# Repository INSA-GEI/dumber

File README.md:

# Dumber

Depot du projet de temps reel 4eme année au departement GEI de l'INSA Toulouse.

## Repertoires
- hardware : contient les plans pour la partie mecanique du robot et de son chargeur, ainsi que les plans de conception des PCB du robot, du chargeur, de l'adaptateur Xbee pour la raspberry  et les plans des CAP du robot
- software: rassemble les parties logicielles du robot, du chargeur, les bibliotheques et superviseur coté raspberry et l'interface Web
- doc: contient les sujets de TD et TP
- aruco_markers: Script de generation des tags (aruco) utilisés sur les robots

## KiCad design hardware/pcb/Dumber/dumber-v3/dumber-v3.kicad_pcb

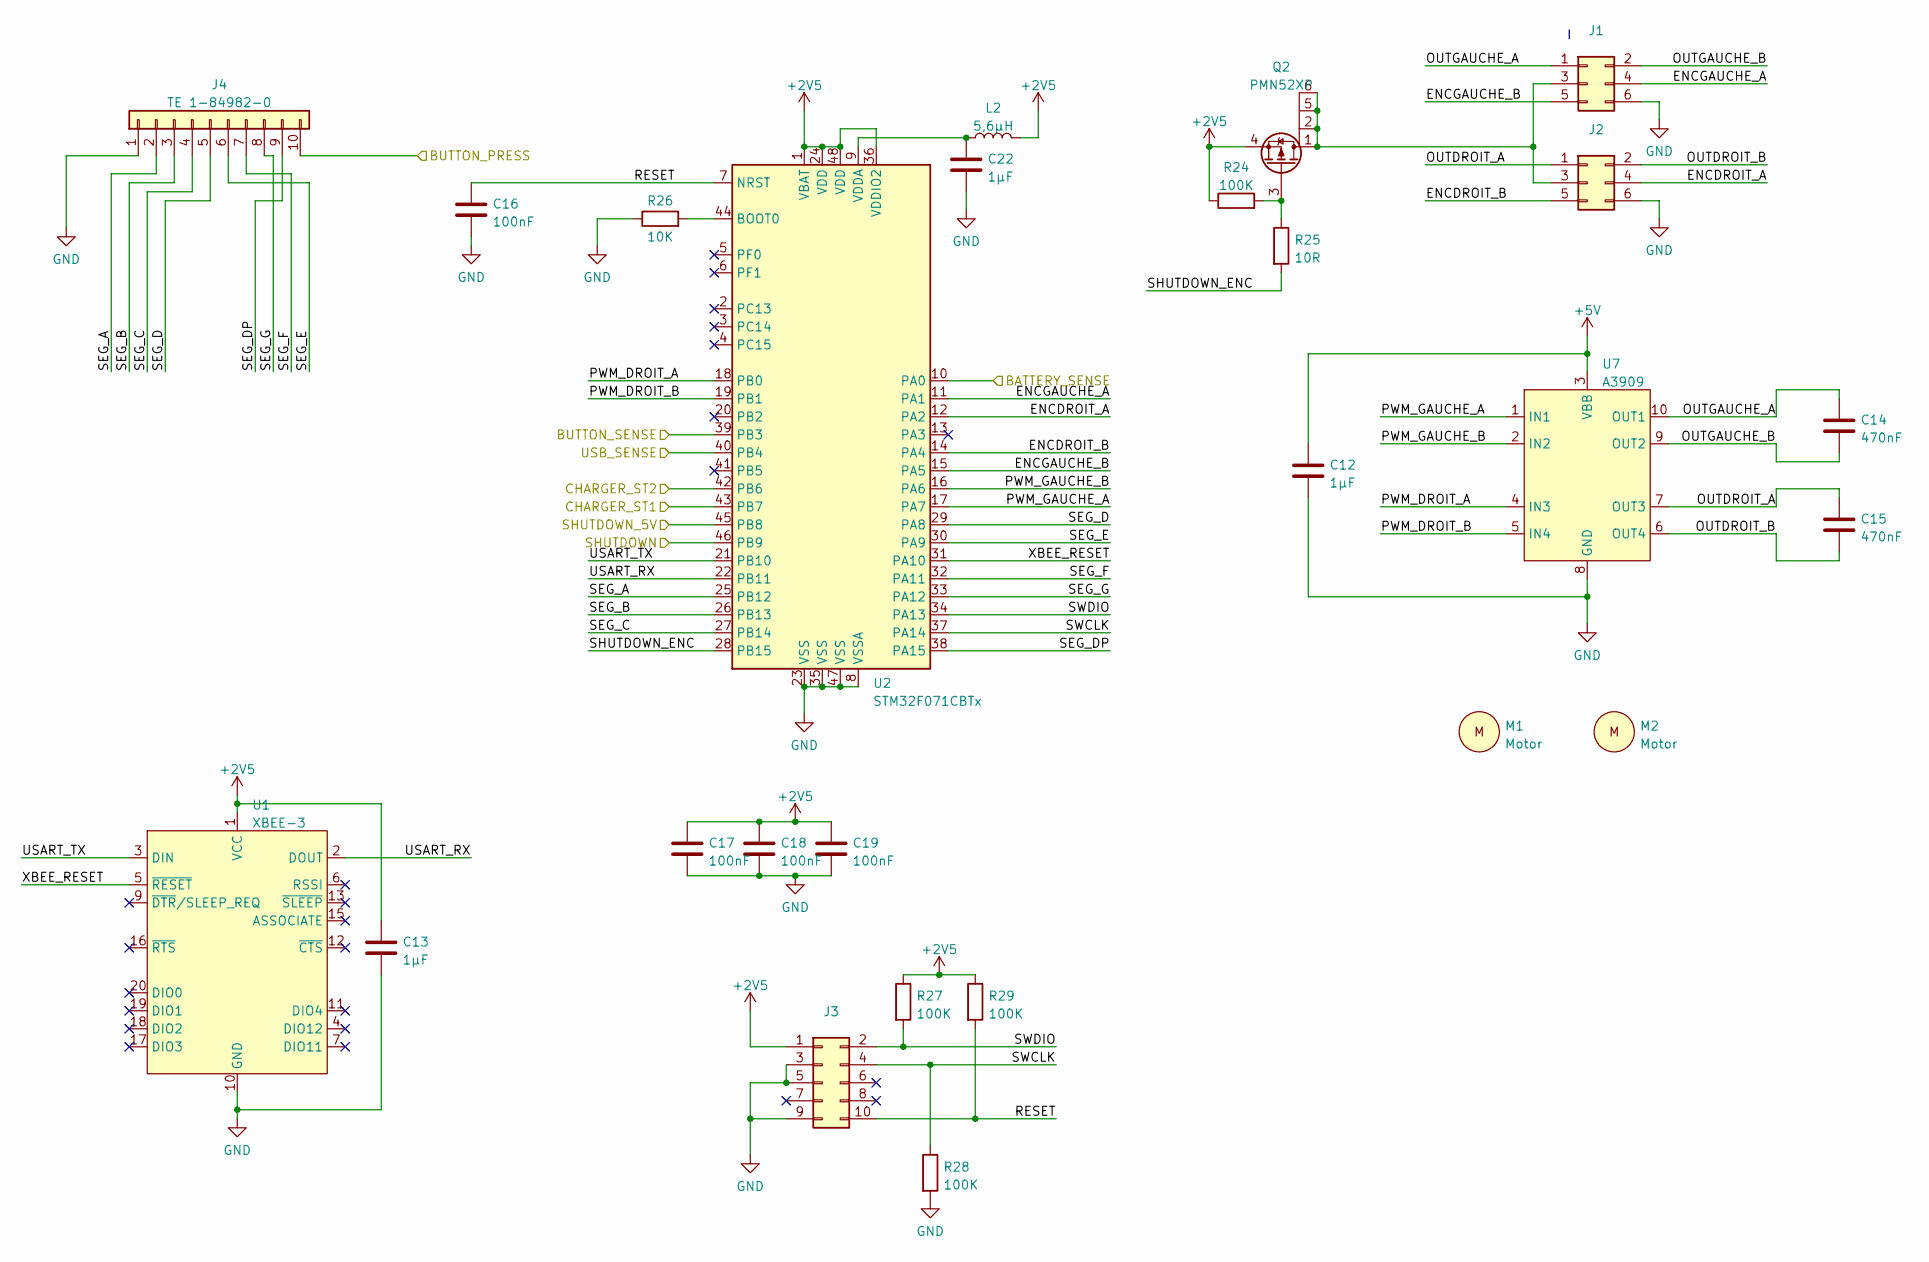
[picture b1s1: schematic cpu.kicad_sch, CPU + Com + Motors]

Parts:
C12, C13, C22: 1µF; C_0805_2012Metric
C14, C15: 470nF; C_0805_2012Metric
C16, C17, C18, C19: 100nF; C_0805_2012Metric
J1, J2: Conn_02x03_Odd_Even; IDC-Header_2x03_P2.54mm_Vertical
J3: Conn_02x05_Odd_Even; PinHeader_2x05_P1.27mm_Horizontal
J4: TE 1-84982-0
L2: 5,6µH; L_1812_4532Metric
M1, M2: Motor; Motor Pololu HPCB with encoder
Q2: PMN52XP; TSOP-6_1.65x3.05mm_P0.95mm
R24, R27, R28, R29: 100K; R_0805_2012Metric
R25: 10R; R_0805_2012Metric
R26: 10K; R_0805_2012Metric
U1: XBEE-3; XBEE-3-TH
U2: STM32F071CBTx; LQFP-48_7x7mm_P0.5mm
U7: A3909; SSOP-10_3.9x4.9mm_P1.00mm

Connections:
+2V5: C13.1, C17.1, C18.1, C19.1, J3.1, L2.2, Q2.4 (S), R24.1, R27.1, R29.1, U1.1 (VCC), U2.1 (VBAT), U2.24 (VDD), U2.36 (VDDIO2), U2.48 (VDD); also elsewhere on the board
+5V: C12.1, U7.3 (VBB); also elsewhere on the board
/Cpu/BATTERY_SENSE: U2.10 (PA0); also elsewhere on the board
/Cpu/BUTTON_PRESS: J4.10; also elsewhere on the board
/Cpu/BUTTON_SENSE: U2.39 (PB3); also elsewhere on the board
/Cpu/CHARGER_ST1: U2.43 (PB7); also elsewhere on the board
/Cpu/CHARGER_ST2: U2.42 (PB6); also elsewhere on the board
/Cpu/ENCDROIT_A: J2.4, U2.12 (PA2)
/Cpu/ENCDROIT_B: J2.5, U2.14 (PA4)
/Cpu/ENCGAUCHE_A: J1.4, U2.11 (PA1)
/Cpu/ENCGAUCHE_B: J1.5, U2.15 (PA5)
/Cpu/OUTDROIT_A: C15.1, J2.1, U7.7 (OUT3)
/Cpu/OUTDROIT_B: C15.2, J2.2, U7.6 (OUT4)
/Cpu/OUTGAUCHE_A: C14.1, J1.1, U7.10 (OUT1)
/Cpu/OUTGAUCHE_B: C14.2, J1.2, U7.9 (OUT2)
/Cpu/PWM_DROIT_A: U2.18 (PB0), U7.4 (IN3)
/Cpu/PWM_DROIT_B: U2.19 (PB1), U7.5 (IN4)
/Cpu/PWM_GAUCHE_A: U2.17 (PA7), U7.1 (IN1)
/Cpu/PWM_GAUCHE_B: U2.16 (PA6), U7.2 (IN2)
/Cpu/RESET: C16.1, J3.10, R29.2, U2.7 (NRST)
/Cpu/SEG_A: J4.2, U2.25 (PB12)
/Cpu/SEG_B: J4.3, U2.26 (PB13)
/Cpu/SEG_C: J4.4, U2.27 (PB14)
/Cpu/SEG_D: J4.5, U2.29 (PA8)
/Cpu/SEG_DP: J4.9, U2.38 (PA15)
/Cpu/SEG_E: J4.6, U2.30 (PA9)
/Cpu/SEG_F: J4.7, U2.32 (PA11)
/Cpu/SEG_G: J4.8, U2.33 (PA12)
/Cpu/SHUTDOWN: U2.46 (PB9); also elsewhere on the board
/Cpu/SHUTDOWN_5V: U2.45 (PB8); also elsewhere on the board
/Cpu/SHUTDOWN_ENC: R25.2, U2.28 (PB15)
/Cpu/SWCLK: J3.4, R28.1, U2.37 (PA14)
/Cpu/SWDIO: J3.2, R27.2, U2.34 (PA13)
/Cpu/USART_RX: U1.2 (DOUT), U2.22 (PB11)
/Cpu/USART_TX: U1.3 (DIN), U2.21 (PB10)
/Cpu/USB_SENSE: U2.40 (PB4); also elsewhere on the board
/Cpu/XBEE_RESET: U1.5 (~RESET), U2.31 (PA10)
GND: C12.2, C13.2, C16.2, C17.2, C18.2, C19.2, C22.2, J1.6, J2.6, J3.3, J3.5, J3.9, J4.1, R26.1, R28.2, U1.10 (GND), U2.8 (VSSA), U2.23 (VSS), U2.35 (VSS), U2.47 (VSS), U7.8 (GND); also elsewhere on the board
unnamed: J1.3, J2.3, Q2.1 (D), Q2.2 (D), Q2.5 (D), Q2.6 (D)
unnamed: Q2.3 (G), R24.2, R25.1
unnamed: R26.2, U2.44 (BOOT0)
unnamed: C22.1, L2.1, U2.9 (VDDA)

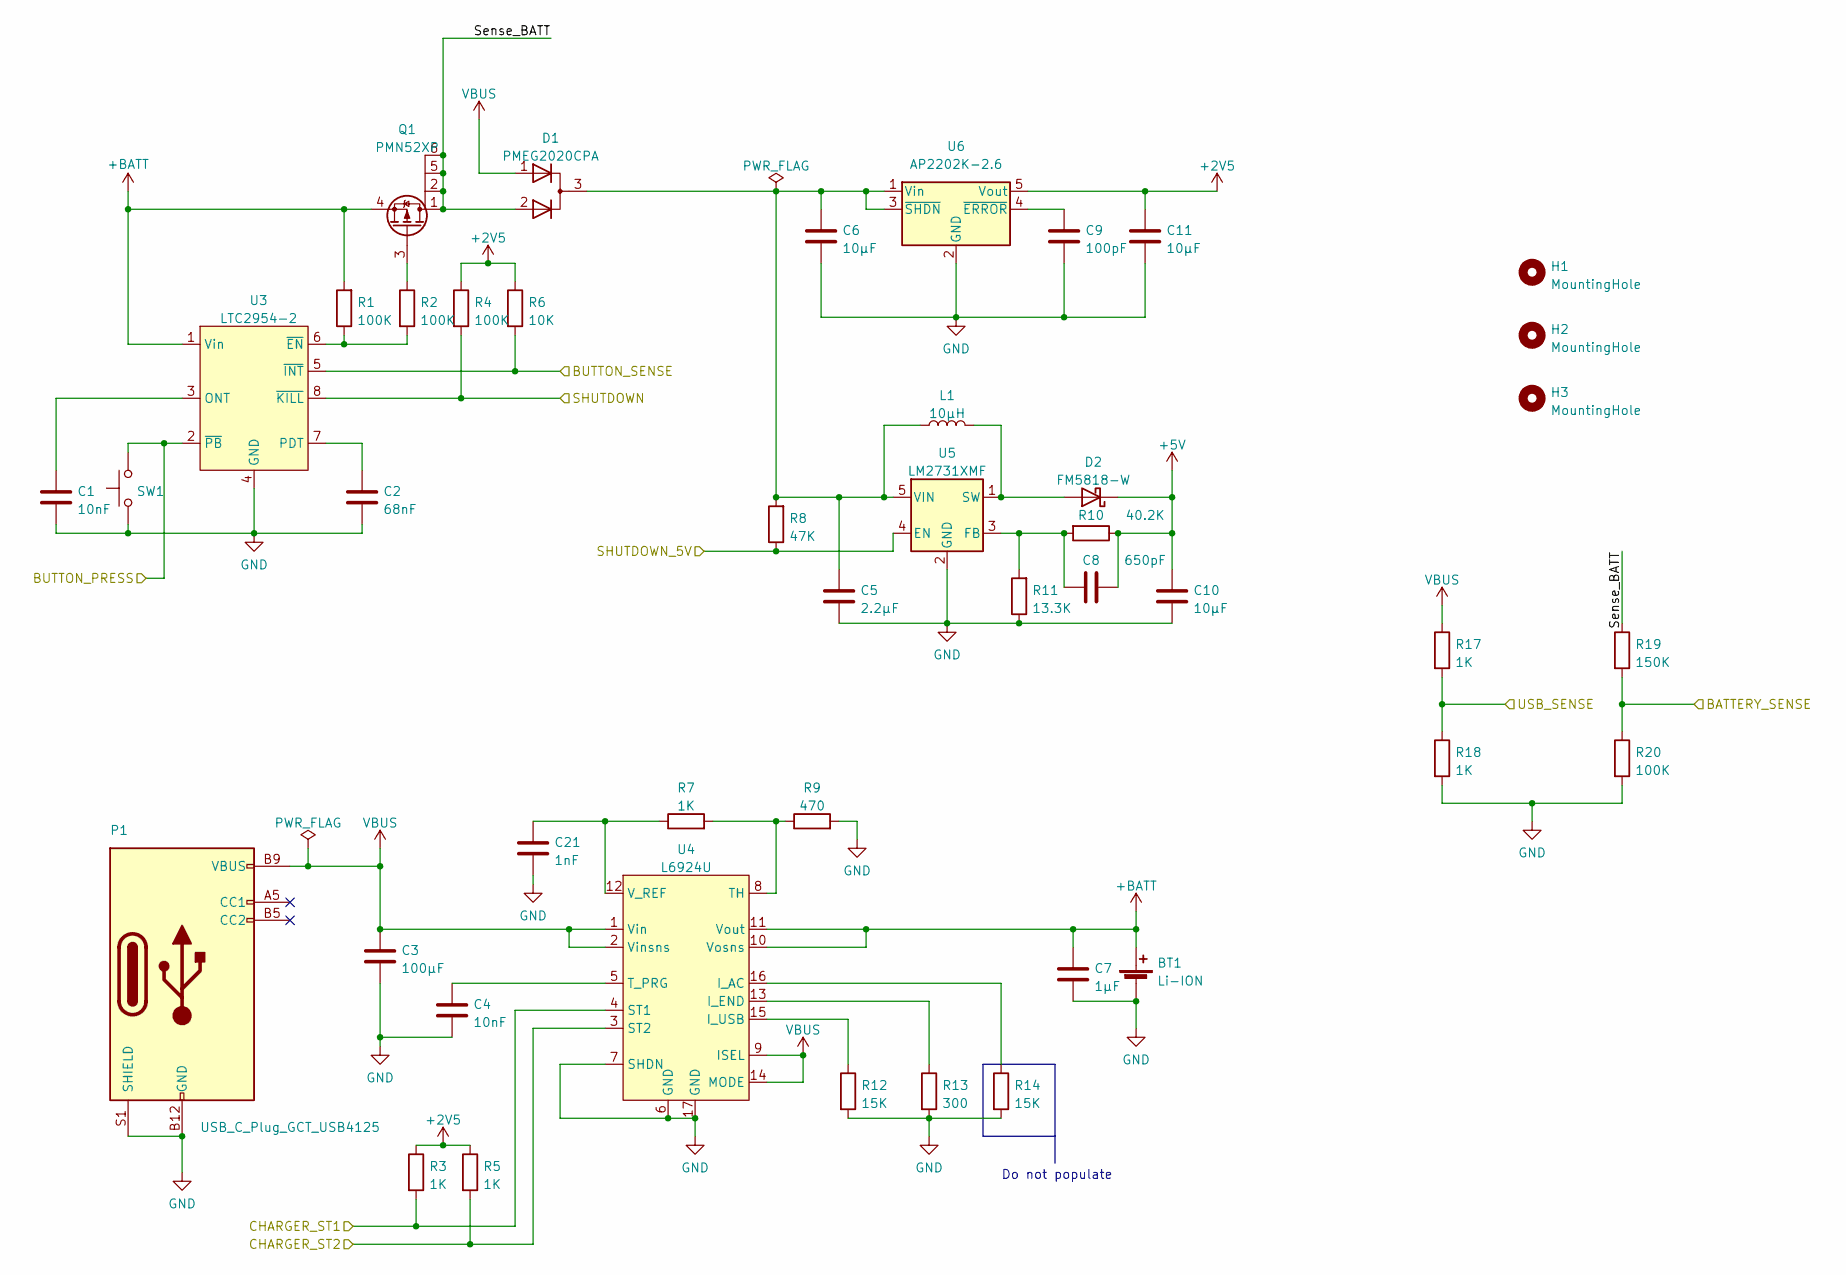
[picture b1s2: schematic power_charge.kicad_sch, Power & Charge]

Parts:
BT1: Li-ION; Battery-14500
C1, C4: 10nF; C_0805_2012Metric
C2: 68nF; C_0805_2012Metric
C3: 100µF; C_1210_3225Metric
C5: 2.2µF; C_0805_2012Metric
C6, C11: 10µF; C_0805_2012Metric
C7: 1µF; C_0805_2012Metric
C8: 650pF; C_0805_2012Metric
C9: 100pF; C_0805_2012Metric
C10: 10µF; C_1210_3225Metric
C21: 1nF; C_0805_2012Metric
D1: PMEG2020CPA; Nexperia_SOT-1061
D2: FM5818-W; D_SMA
H1, H2, H3: MountingHole; MountingHole_3.2mm_M3_ISO14580
L1: 10µH; L_Bourns_SRP7028A_7.3x6.6mm
P1: USB_C_Plug_GCT_USB4125; USB_C_Receptacle_GCT_USB4125
Q1: PMN52XP; TSOP-6_1.65x3.05mm_P0.95mm
R1, R2, R4, R20: 100K; R_0805_2012Metric
R3, R5, R7, R17, R18: 1K; R_0805_2012Metric
R6: 10K; R_0805_2012Metric
R8: 47K; R_0805_2012Metric
R9: 470; R_0805_2012Metric
R10: 40.2K; R_0805_2012Metric
R11: 13.3K; R_0805_2012Metric
R12, R14: 15K; R_0805_2012Metric
R13: 300; R_0805_2012Metric
R19: 150K; R_0805_2012Metric
SW1: SW_Push; Panasonic_EVQPUJ_EVQPUA
U3: LTC2954-2; SOT-23-8
U4: L6924U; L6924UTR
U5: LM2731XMF; SOT-23-5
U6: AP2202K-2.6; SOT-23-5

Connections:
+2V5: C11.1, R3.1, R4.1, R5.1, R6.1, U6.5 (Vout); also elsewhere on the board
+5V: C8.2, C10.1, D2.1 (K), R10.1; also elsewhere on the board
+BATT: BT1.1 (+), C7.1, Q1.4 (S), R1.2, U3.1 (Vin), U4.10 (Vosns), U4.11 (Vout)
/Cpu/BATTERY_SENSE: R19.2, R20.1; also elsewhere on the board
/Cpu/BUTTON_PRESS: SW1.2, U3.2 (~PB); also elsewhere on the board
/Cpu/BUTTON_SENSE: R6.2, U3.5 (~INT); also elsewhere on the board
/Cpu/CHARGER_ST1: R3.2, U4.4 (ST1); also elsewhere on the board
/Cpu/CHARGER_ST2: R5.2, U4.3 (ST2); also elsewhere on the board
/Cpu/SHUTDOWN: R4.2, U3.8 (~KILL); also elsewhere on the board
/Cpu/SHUTDOWN_5V: R8.1, U5.4 (EN); also elsewhere on the board
/Cpu/USB_SENSE: R17.2, R18.1; also elsewhere on the board
/Power_Charge/Sense_BATT: D1.2 (K), Q1.1 (D), Q1.2 (D), Q1.5 (D), Q1.6 (D), R19.1
GND: BT1.2 (-), C1.2, C2.2, C3.2, C4.2, C5.2, C6.2, C7.2, C9.2, C10.2, C11.2, C21.2, P1.A12 (GND), P1.B12 (GND), P1.S1 (SHIELD), R9.2, R11.1, R12.2, R13.2, R14.2, R18.2, R20.2, SW1.1, U3.4 (GND), U4.6 (GND), U4.7 (SHDN), U4.17 (GND), U5.2 (GND), U6.2 (GND); also elsewhere on the board
unnamed: C1.1, U3.3 (ONT)
unnamed: C2.1, U3.7 (PDT)
unnamed: C4.1, U4.5 (T_PRG)
unnamed: C5.1, C6.1, D1.3 (A), L1.1, R8.2, U5.5 (VIN), U6.1 (Vin), U6.3 (~SHDN)
unnamed: C8.1, R10.2, R11.2, U5.3 (FB)
unnamed: C9.1, U6.4 (~ERROR)
unnamed: C21.1, R7.1, U4.12 (V_REF)
unnamed: D2.2 (A), L1.2, U5.1 (SW)
unnamed: Q1.3 (G), R2.1
unnamed: R1.1, R2.2, U3.6 (~EN)
unnamed: R7.2, R9.1, U4.8 (TH)
unnamed: R12.1, U4.15 (I_USB)
unnamed: R13.1, U4.13 (I_END)
unnamed: R14.1, U4.16 (I_AC)
VBUS: C3.1, D1.1 (K), P1.A9 (VBUS), P1.B9 (VBUS), R17.1, U4.1 (Vin), U4.2 (Vinsns), U4.9 (ISEL), U4.14 (MODE)

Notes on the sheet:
Do not populate

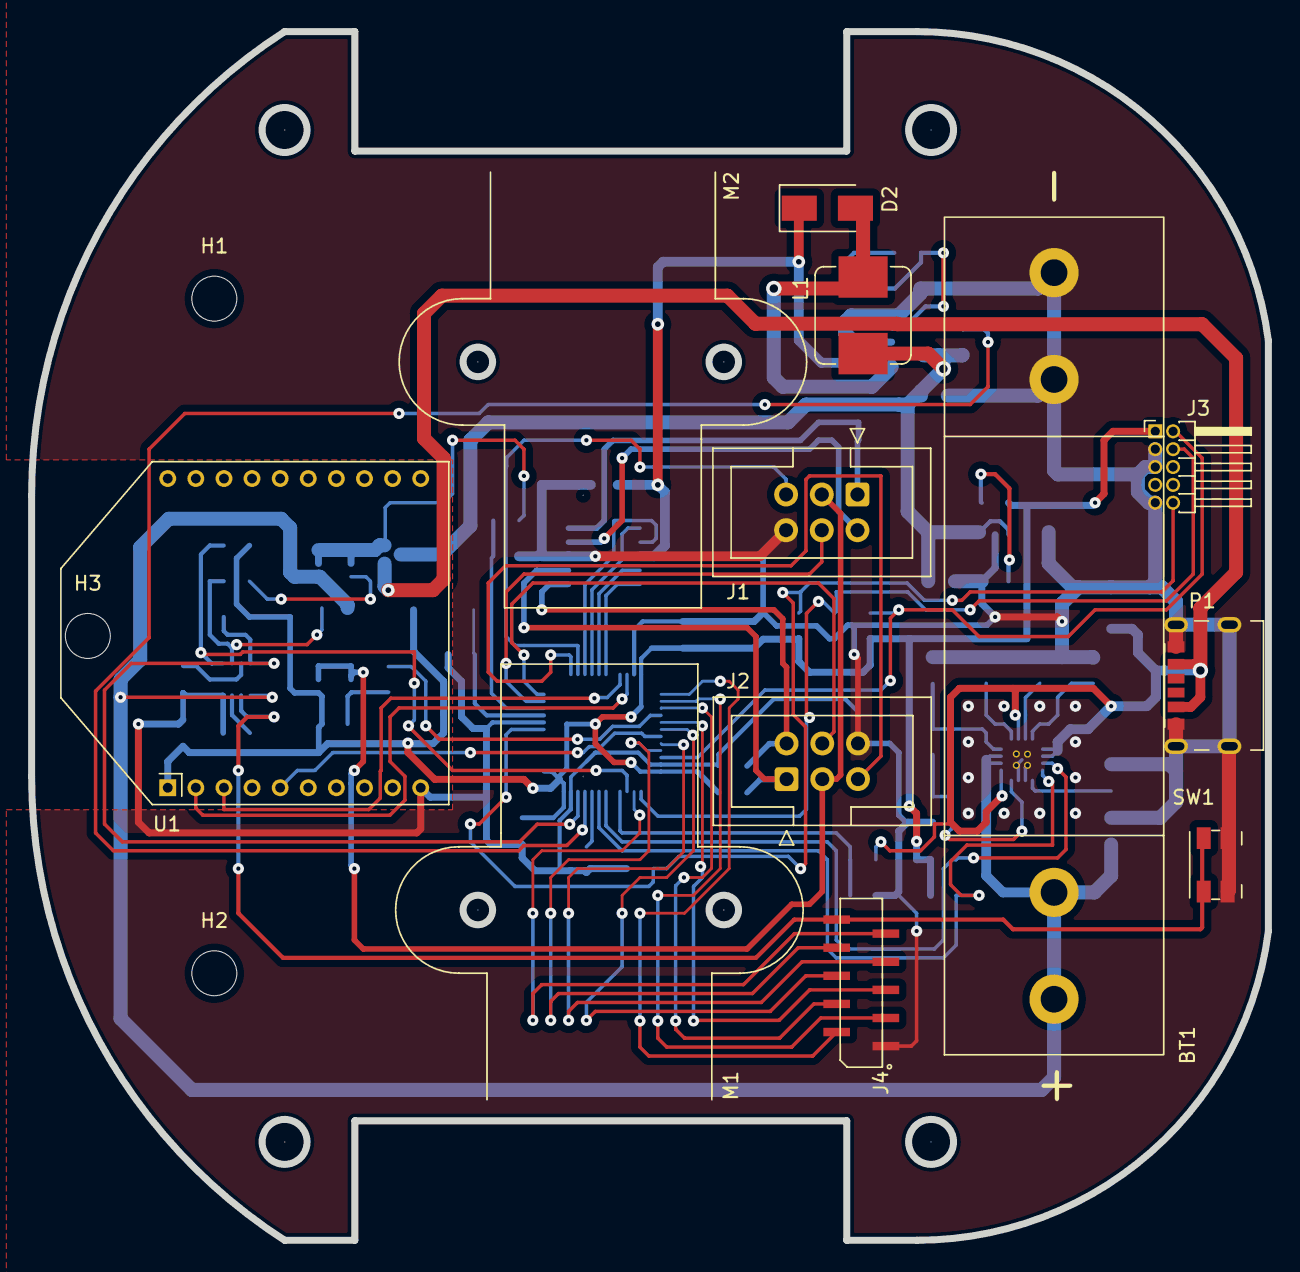
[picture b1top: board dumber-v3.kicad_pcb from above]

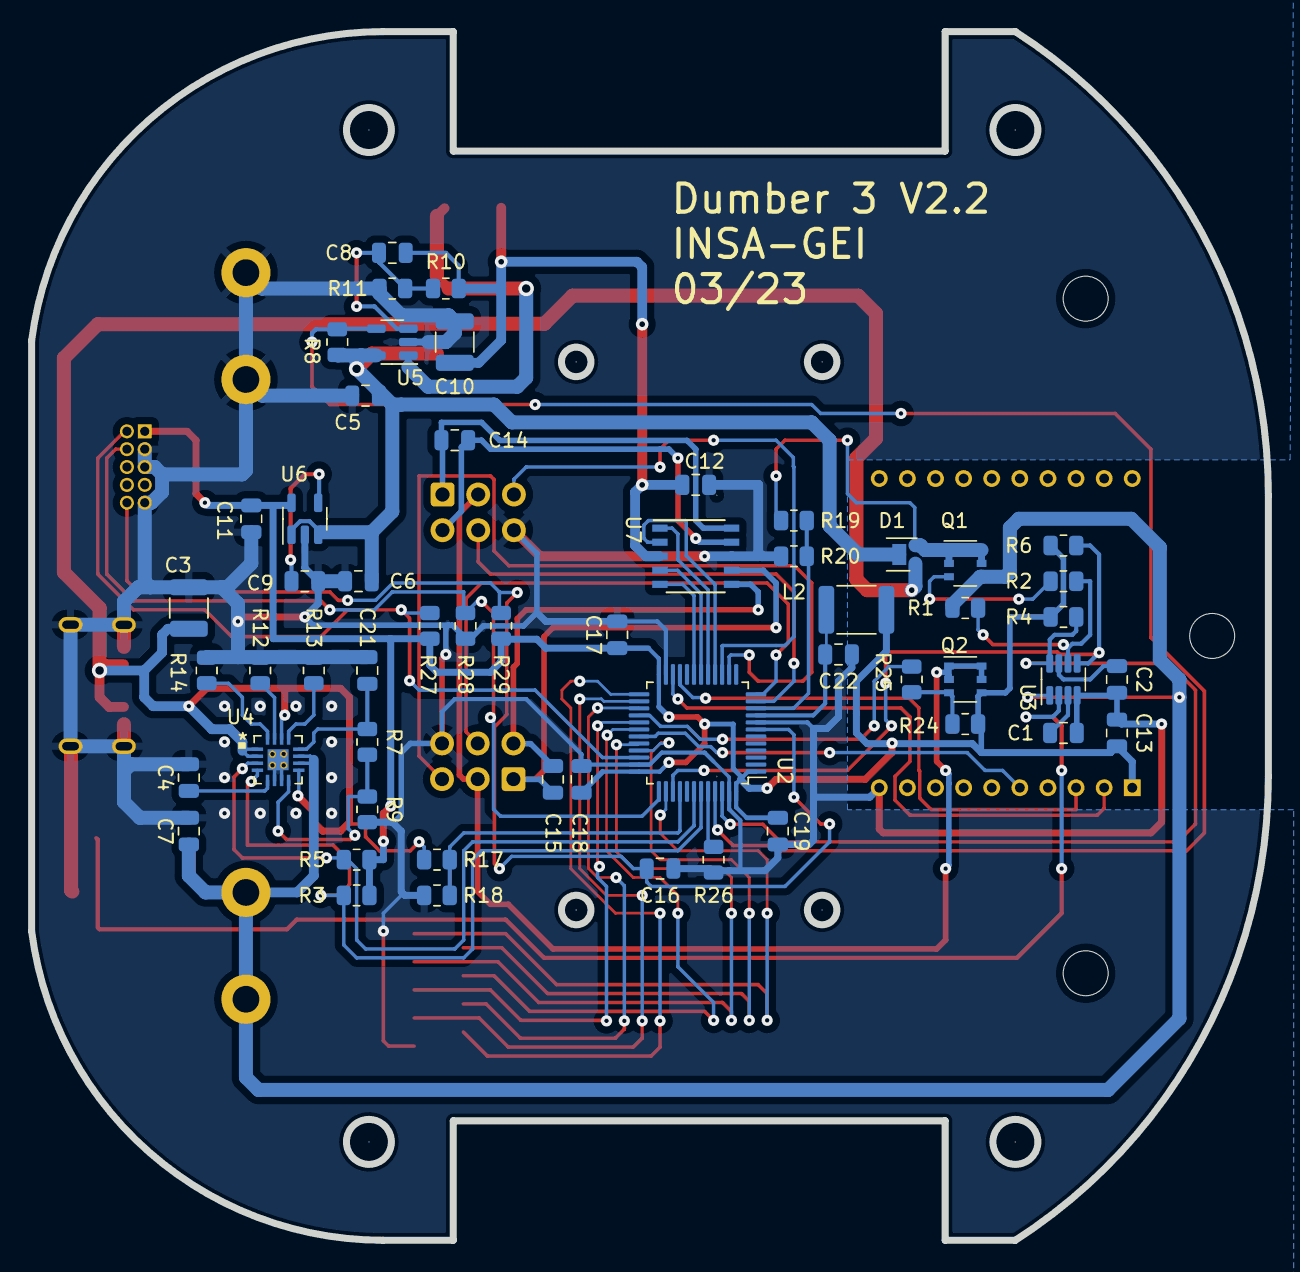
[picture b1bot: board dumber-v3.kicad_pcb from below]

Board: 2 copper layers, 88.0 x 86.0 mm, 70 parts (55 on the bottom side), 59 nets.

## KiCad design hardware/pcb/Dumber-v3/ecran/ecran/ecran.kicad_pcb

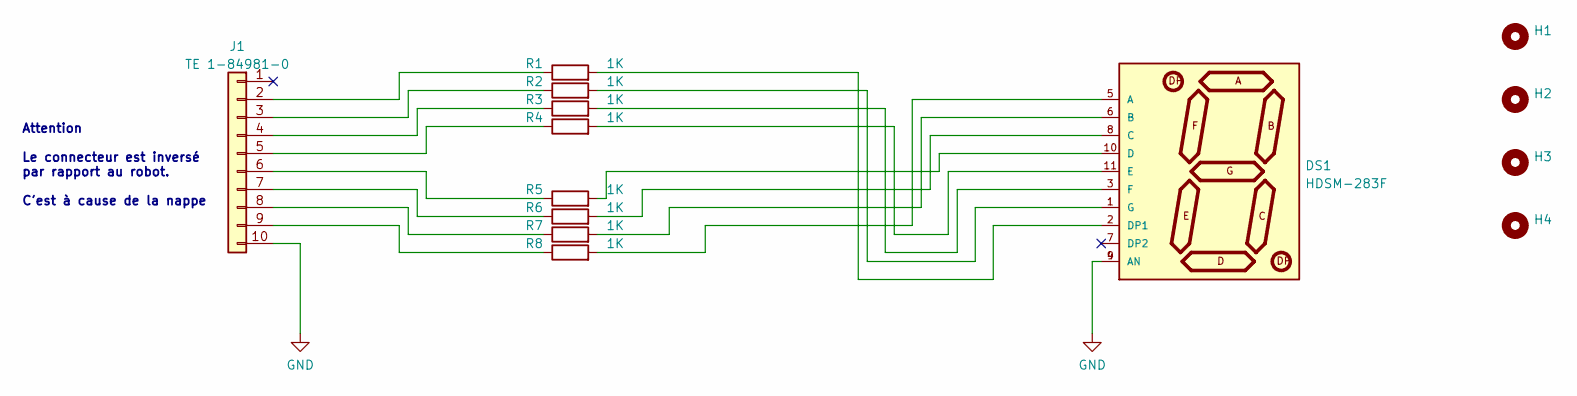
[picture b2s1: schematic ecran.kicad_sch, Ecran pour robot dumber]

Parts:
DS1: HDSM-283F; LED_HDSM-283F
H1, H2, H3, H4: MountingHole; MountingHole_3mm
J1: TE 1-84981-0
R1, R2, R3, R4, R5, R6, R7, R8: 1K; R_0805_2012Metric

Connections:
GND: DS1.4 (AN), DS1.9 (AN), J1.10
unnamed: DS1.1 (G), R2.2
unnamed: DS1.2 (DP1), R1.2
unnamed: DS1.3 (F), R3.2
unnamed: DS1.5 (A), R8.2
unnamed: DS1.6 (B), R7.2
unnamed: DS1.8 (C), R6.2
unnamed: DS1.10 (D), R5.2
unnamed: DS1.11 (E), R4.2
unnamed: J1.2, R1.1
unnamed: J1.3, R2.1
unnamed: J1.4, R3.1
unnamed: J1.5, R4.1
unnamed: J1.6, R5.1
unnamed: J1.7, R6.1
unnamed: J1.8, R7.1
unnamed: J1.9, R8.1

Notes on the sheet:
Attention Le connecteur est inversé par rapport au robot. C'est à cause de la nappe

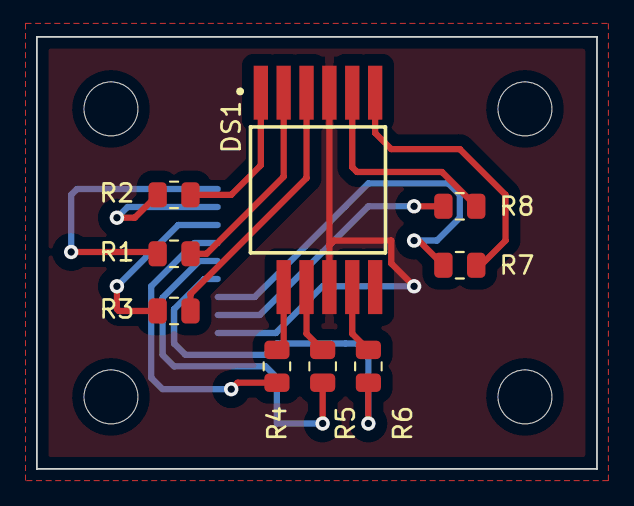
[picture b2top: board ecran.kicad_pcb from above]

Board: 2 copper layers, 31.1 x 24.0 mm, 14 parts (1 on the bottom side), 17 nets.

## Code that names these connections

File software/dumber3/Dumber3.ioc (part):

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Mcu.Name=STM32L071C(B-Z)Tx
Mcu.Package=LQFP48
Mcu.UserName=STM32L071CBTx
PA0.GPIOParameters=GPIO_Label
PA0.GPIO_Label=BATTERY_SENSE
PA0.Mode=IN0
PA0.Signal=ADC_IN0
PA1.GPIOParameters=GPIO_Label
PA1.GPIO_Label=ENC_PHA_GAUCHE
PA1.Signal=GPIO_Input
PA10.GPIOParameters=PinState,GPIO_Label
PA10.GPIO_Label=XBEE_RESET
PA10.PinState=GPIO_PIN_RESET
PA10.Signal=GPIO_Output
PA11.GPIOParameters=GPIO_Label
PA11.GPIO_Label=LED_SEG_F
PA11.Signal=GPIO_Output
PA12.GPIOParameters=GPIO_Label
PA12.GPIO_Label=LED_SEG_G
PA12.Signal=GPIO_Output
PA13.Mode=Serial_Wire
PA13.Signal=SYS_SWDIO
PA14.Mode=Serial_Wire
PA14.Signal=SYS_SWCLK
PA15.GPIOParameters=GPIO_Label
PA15.GPIO_Label=LED_SEG_DP
PA15.Signal=GPIO_Output
PA2.GPIOParameters=GPIO_Label
PA2.GPIO_Label=ENC_PHA_DROIT
PA2.Signal=S_TIM21_CH1
PA5.GPIOParameters=GPIO_Label
PA5.GPIO_Label=ENC_PHB_GAUCHE
PA5.Signal=S_TIM2_CH1
PA6.GPIOParameters=GPIO_Label
PA6.GPIO_Label=PWM_B_GAUCHE
PA6.Signal=S_TIM3_CH1
PA7.GPIOParameters=GPIO_Label
PA7.GPIO_Label=PWM_A_GAUCHE
PA7.Signal=S_TIM3_CH2
PA8.GPIOParameters=GPIO_Label
PA8.GPIO_Label=LED_SEG_D
PA8.Signal=GPIO_Output
PA9.GPIOParameters=GPIO_Label
PA9.GPIO_Label=LED_SEG_E
PA9.Signal=GPIO_Output
PB0.GPIOParameters=GPIO_Speed,GPIO_Label
PB0.GPIO_Label=PWM_A_DROIT
PB0.GPIO_Speed=GPIO_SPEED_FREQ_LOW
PB0.Signal=S_TIM3_CH3
PB1.GPIOParameters=GPIO_Speed,GPIO_Label
PB1.GPIO_Label=PWM_B_DROIT
PB1.GPIO_Speed=GPIO_SPEED_FREQ_LOW
PB1.Signal=S_TIM3_CH4
PB10.GPIOParameters=GPIO_Speed,GPIO_Label
PB10.GPIO_Label=USART_TX
PB10.GPIO_Speed=GPIO_SPEED_FREQ_LOW
PB10.Mode=Asynchronous
PB10.Signal=LPUART1_TX
PB11.GPIOParameters=GPIO_Speed,GPIO_Label
PB11.GPIO_Label=USART_RX
PB11.GPIO_Speed=GPIO_SPEED_FREQ_LOW
PB11.Mode=Asynchronous
PB11.Signal=LPUART1_RX
PB12.GPIOParameters=GPIO_Speed,PinState,GPIO_Label
PB12.GPIO_Label=LED_SEG_A
PB12.GPIO_Speed=GPIO_SPEED_FREQ_LOW
PB12.PinState=GPIO_PIN_RESET
PB12.Signal=GPIO_Output
PB13.GPIOParameters=GPIO_Speed,GPIO_Label
PB13.GPIO_Label=LED_SEG_B
PB13.GPIO_Speed=GPIO_SPEED_FREQ_LOW
PB13.Signal=GPIO_Output
PB14.GPIOParameters=GPIO_Speed,GPIO_Label
PB14.GPIO_Label=LED_SEG_C
PB14.GPIO_Speed=GPIO_SPEED_FREQ_LOW
PB14.Signal=GPIO_Output
PB15.GPIOParameters=PinState,GPIO_Label
PB15.GPIO_Label=SHUTDOWN_ENCODERS
PB15.PinState=GPIO_PIN_SET
PB15.Signal=GPIO_Output
PB3.GPIOParameters=GPIO_Label,GPIO_ModeDefaultEXTI
PB3.GPIO_Label=BUTTON_SENSE
PB3.GPIO_ModeDefaultEXTI=GPIO_MODE_IT_FALLING
PB3.Signal=GPXTI3
PB4.GPIOParameters=GPIO_Label,GPIO_ModeDefaultEXTI
PB4.GPIO_Label=USB_SENSE
PB4.GPIO_ModeDefaultEXTI=GPIO_MODE_IT_RISING_FALLING
PB4.Signal=GPXTI4
PB6.GPIOParameters=GPIO_Label
PB6.GPIO_Label=CHARGER_ST2
PB6.Signal=GPIO_Input
PB7.GPIOParameters=GPIO_Label
PB7.GPIO_Label=CHARGER_ST1
PB7.Signal=GPIO_Input
PB8.GPIOParameters=GPIO_Label
PB8.GPIO_Label=SHUTDOWN_5V
PB8.Signal=GPIO_Output
PB9.GPIOParameters=PinState,GPIO_Label,GPIO_ModeDefaultOutputPP
PB9.GPIO_Label=SHUTDOWN
PB9.GPIO_ModeDefaultOutputPP=GPIO_MODE_OUTPUT_OD
PB9.PinState=GPIO_PIN_SET
PB9.Signal=GPIO_Output
RCC.HSE_VALUE=8000000
RCC.SYSCLKFreq_VALUE=6000000
RCC.SYSCLKSource=RCC_SYSCLKSOURCE_PLLCLK
board=custom

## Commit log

2018-08-27 initialisation de la branche stable, sans repertoire "incubateur"
2018-10-08 reorganisation du code de dumber et passage à une version recente
2018-10-10 Version 1.3 du soft robot
2018-10-10 Version 1.4 du soft robot. Rajout de la commande PowerOff
2018-10-12 robot class + serial class ok. Tcp server class seems ok
2018-10-16 reorganisation du repertoire superviseur-robot + passage à Cmake
2018-10-19 Last commit to branch master.
    after that next commits will be in branch dev or stable
2018-10-19 Code stable, serveur included in binary
2018-10-25 ajout du serveur dans le moniteur
2018-11-07 sauvegarde
2018-11-07 gestion des flux binaires
2018-11-08 Version du moniteur proche de la version finale, petits bugs corrigés dans le testeur du superviseur
2018-11-08 nettoyage de la branche master
2018-11-08 ajout de la documentation du moniteur
2018-11-11 rajout du support udp
2018-11-11 petite correction
2018-11-12 ajout de traceur pour la qualité d'image
2018-11-12 small modifs
2018-11-12 UDP a peu pres OK
2018-11-13 ajout des commentaires, version candidate pour la version stable 2.0
2018-12-14 mise au propre de la branche stable avec reprise du travail
2018-12-14 passage au tout objet + messagerie
2018-12-19 passage au tout objet en cours
2018-12-21 Classe comRobot partiellement debuggée
2019-01-04 images are now sent using base64. 40fps on localhost, test to be done on raspberry
2019-01-09 aruco rajouté + script pour compiler et installer opencv avec le support aruco
2019-01-10 aruco ok sur raspberry + correction de la configuration du projet netbeans pour raspberry
2019-01-14 Ajout des sources latex des specifications
2019-01-14 Ajout du guide pour les etudiants
2019-01-15 rajouts des commentaires (Demande #35) Creation d'une classe imageWidget dans le moniteur (demande #43) modifications du comportement des fleches dans le moniteur (demande #41) Suppression de relicat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
2019-01-17 Reorganisation de qq fichier Demande #42: Migrer le code sous xenomai
2019-01-17 remove not_for_students directory
2019-01-19 ajout partie latex conception
2019-01-23 Nouvelle branche pour les journées portes ouvertes 2019
2019-01-23 demonstrateur pour les JPO2019
2019-01-23 Corrections apres essai en salle de TP
2019-01-23 Modification suite à tests en salle de TP
2019-01-24 Ajustement de la vitesse de capture des images
2019-02-08 nouvelle branche double_port pour tester un port special pour les images
2019-02-08 projet init
2019-02-11 mise a jour dossie de conception
2019-02-11 mise a jour specification
2019-02-11 mise a jour guide et code
2019-02-11 Oubli de fichier
2019-03-05 ajout rapport étudiant
2019-04-01 Typo
2019-04-11 update lib
2019-04-11 correction sujets
2019-04-11 Re-merge depuis la branche dev du repertoire software/raspberry/superviseur-robot qui n'etait pas à jour
2019-04-11 Correction sur le moniteur pour prendre an charge les messages de timeout et d'erreur de communication + suppression du timer et bouton getbattery
2019-05-07 typos
2019-05-20 wd remis à 0 en cas de succes
2019-05-29 Correcting comrobot documentation write
2019-05-29 Adding a line of documentation for creating Img *
2019-05-29 Removing delete condition (img) from commonitor
2019-05-29 Typo Rapport étudiant and correcting labels for better ref
2020-02-23 ajout configuration plugin c/c++ netbeans
2020-03-14 add robot simulator
2020-03-14 simulateur: ajout temps de réponse et erreur, comrobot : ajout msgAnswer adequat a la reponse
2020-03-19 update simulator with watchdog, ping, reset, poweroff and relaod commands
2020-03-30 keep supervisor alive if robot is killed
2020-03-30 fix close
2020-04-05 add carriage return for robot communication with the simulator
2020-04-06 add open(string host, int port)
2020-04-17 localhost by default, reconnexion available, the panel control is not activated if the robot is not start
2020-04-17 Revert "localhost by default, reconnexion available, the panel control is not activated if the robot is not start"
    This reverts commit f98343aca4a56858d333d98bfed6ae738552c4b6.
2020-04-17 localhost by default, reconnexion ok, panel control ok
2020-05-11 En liaison avec cette discussion: https://discordapp.com/channels/691221456792584192/691221456792584196/709295769458442260
2020-06-23 Ajout de la doc technique
2021-03-02 fix wrong memory usage.
2022-02-04 Multiple chose + moniteur en python (ligne de commande)
2022-02-04 trucs autour des aruco
2022-02-04 ajout d'un moniteur en python et ligne de commande
2022-02-07 ajout de commentaire dans monitor-python.py
2022-02-10 Mise a jour git
2022-02-10 Add first funcionality
2022-02-10 Fin CheckBattery
2022-02-10 Create task for start with watchdog
2022-02-11 Add watchdog
2022-02-11 Add error message when monitor connection is lost
2022-02-11 Add stop system
2022-02-11 Add stop functionality and refactor
2022-02-16 Now tested
2022-02-18 Finished
2022-03-18 Recuperation du projet CubeIDe des robots depuis la branche jpo2019
2022-03-18 Recuperation du projet chargeur depuis la branche dev
2022-03-18 conversion du project cubeide du robot pour cubeide 1.7
2022-03-25 premier script pour compilation automatique du noyau xenomai
2022-03-25 Ajout d'une option en ligne de commande pour compiler uniquement
2022-03-25 Correction sur lib paramiko
2022-03-25 Ajout des fichier config et patch pour la 4.14.37
2022-03-25 Correction sur ipipe-core-4.14.37-rpi.patch
2022-05-30 nouvelle version de dumber
2022-06-08 Debut réalisation PCB
2022-06-10 Schema complet, projet logiciel demarré
2022-06-14 PCB fini
2022-07-07 nouvelle version pcb dumber + nouvelle version monietur en QT
2022-07-08 rajout de fichiers .gitignore
2022-08-22 modification mineur du pcb
2022-08-22 suppression du moniteur C# et ajout d'un moniteur python/qt
2022-08-31 Correction de plusieurs erreurs sur la PCB, passé en version 1.1
2022-09-15 premiers modules du firwmare dumber 3
2022-09-23 changement de puce vers STM32L071CBT6
2022-09-23 Modification du PCB suite au passage au MCU STM32L071CBT6
2022-10-18 sauvegarde avant basculement de branche
2022-10-18 oubli de .cproject .mxproject
2022-10-18 Projet netbeans converti vers cobalt. Raspicam non necessaire desormais
2022-10-19 Ajout d'un projet en pthread + ajout support des images sur moniteur
2022-10-20 Ajout de l'affichage de la position dans le moniteur + nettoyage dans le code des superviseurs
2022-10-20 suppression des moniteurs en C# et en python-text
2022-10-20 Dernier correctif pour renforcer l'affichage des images
2022-11-30 Mise a jour PCB et coque. Des fichiers STEP ne sont pas encore remontés car trop gros
2023-02-17 Mise a jour sur les pcbs de dumber v3
2023-03-22 Reorganisation des fichiers du firmware
2023-03-24 remaniement des drivers xbee et commands
2023-03-31 Driver moteurs a finir, le reste est a peu pres en place. Grosse seance de test en prevision (moteurs, xbee, application, commandes, batterie)
2023-04-11 Driver XBEE semble enfin marcher correctement
2023-04-13 asservissement moteur de base OK
2023-04-14 Batterie OK
2023-04-14 PCB V2.2 avec une self sur AVDD
2023-10-06 Gros jardinage
2023-10-06 remarche mais probleme probable de fragmentation memoire
2023-10-09 les commandes marchent, mais les moteurs non: probleme de puce selectionnée dasn l'IDE
2023-10-09 Resolution du probleme de demarrage des moteurs + correction du modele de puce dans le projet STM32cubeIDE
2023-10-10 Ajout de la commande stop (M=0) dasn la liste des commande X-ctu
2023-10-10 Fonction moteur marche a peu pres correctement. Asservissement a revoir cependant
2023-10-10 Rationalisation des messages batterie, la tension n'est plus envoyé que pour test
2023-10-11 creation des niveau de battery, a regler sur banc
2023-10-11 Ajout d'un systeme de panic pour tracer des erreurs irrecuperables
2023-10-12 Premiere version entirement debuggée et fonctionelle
2023-10-12 Preparation de la version dumber3 2.1 et creation de la cible 'Release'
2023-10-20 Debut de la doc dumber v3
2023-11-22 mise à jour de la doc technique du robot
2023-12-18 Mise a jour de la documentation technique du robot v3
2024-01-09 Debut de documentation doxygen + renommage de module
2024-01-11 Documentation finie, reprise potentielle a prevoir pour retirer des balises inutiles
2024-01-11 Corrections de quelques bugs liés à la gestion des commandes + modifications cosmetiques
2024-01-12 Suppression de la tache par defaut créé par Cube MX qui pose probleme quand elle se termine, passage de la memoire dynamique de 1024 octets à 10240 octets, ajout du support du temps d'execution des t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
2024-01-15 Creation d'une nouvelle branche dumber-v2 pour gerer les evolutions sur la generation 2 du robot
2024-01-16 Correction d'un bug uniquement existant hors debug, lié a une mauvaise gestion des chaines de caractere de taille nulle dans VerifyChecksum + reprise des priorité de taches (reduction de la priorité 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
2024-01-23 Mise a jour de la doc et operation de nettoyage du code du robot
2024-01-25 Corrections autour des zones a activer ou deactiver en fonction de l'etat de connexion
2024-01-25 Correction d'un probleme de depassement de capacité sur les commandes Move et Turn, coté robot et coté superviseur
2024-03-21 correction de bugs lorsque le watchdog est actif ainsi que les moteurs + bug lorsque la batterie est faible
2024-03-25 Correction probleme de reset wdt en meme temps que des commandes moteurs + correction bug lorsque l'on relance les moteurs apres un etat Watchdog_Disabled
2024-03-27 modif robot pour overflow
2024-03-27 Correction probleme de build sur netbeans (mauvais merge)
2024-03-27 suppression de monitor-python (mode texte). Conservation uniquement de monitor-python-qt
2024-04-04 ajout d'une version sur pthread
2024-04-04 repertoire build oublié
2025-01-31 Ajout d'aruco pour les nouveaux robots
2025-01-31 Ajout d'une mention au sujet d'unpack200 dans le fichier README.md du superviseur
2025-02-03 Rajout de l'executable unpack200 en cas d'absence sur l'ordinateur
2025-03-21 Version du superviseur en Pthreads, complet (camera, batterie, mouvements), pour test
2026-02-18 modification legere + ajout correction sur l'adaptateur xbee de la Raspberry
2026-02-18 changement de cible par defaut pour le projet superviseur (initialement PC, maintenant RPI)
2026-02-18 rajout des fichiers de configuration de netbeans

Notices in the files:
parts and their libraries:
Copyright 2021 Accelerated Designs. All rights reserved.
